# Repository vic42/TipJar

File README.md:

# TipJar
Vienna Repair Cafe talking tip jar

DESCRIPTION
===========

This is a *talking* tip jar design that is able to differentiate between coins and banknotes to utter two different spoken, sung or screamed messages accordingly.
It is a Lo-Fi approach meant to reduce cost as well as programming effort in order to get it done and ultimately keep it easily reproducible.
Feel free to use and/or comment.

# HOW IT WORKS

The board detects objects in the gap of two photointerrupters and measures the time than an object spends to pass the photointerrupters. If the time is below a certain threshold a coin is detected and one of the sound modules gets activated. if the time is above that threshold a banknote is detected and the other sound module is activated.
This way two different sound messages are played depending on the type of cash thrown into the tip jar.

# HARDWARE

The hardware is prepared for two modes of sound generation:

* sound recorded on one or two Chinese sound modules (e.g. 2 x ISD1820)
* sound generation by the microcontroller itself

Depending on which mode you prefer you can omit some of the components on the PCB

* first option: R7, D2, L2, C5, L1, C3, P2
* second option: BT1, D3, D4, R8, R10, Q3, Q6, P4, P5

There are various options powering the circuit:

* LiPo battery with micro USB power supply as charger
* 5V micro USB power supply only

Depending on if you need battery supply you can leave out some components

* with battery: U2
* without battery: U1, R1, R2, R3, JP1, P3

Warning: the PN2222A SOT23 footprint of the current PCB has base and emitter swapped.

# SOFTWARE

Currently there is a simplistic C program in the repository that switches on the optointerrupters for 1 ms every 10 ms (10% duty cycle saves power) to see if one of them is interrupted by an object. if so, it counts the cycles while the object occludes the detector. If 8 cycles have passed before the detector sees light again a banknote is assumed to have passed the detector. Oterwise the object detected is assumed to have been a coin.

# BUILD

There is a Makefile included with the code. It needs to be adjusted to your AVR-ISP interface in order to upload the code to the microcontroller directly.

# SEE ALSO

* https://repaircafe.wien/

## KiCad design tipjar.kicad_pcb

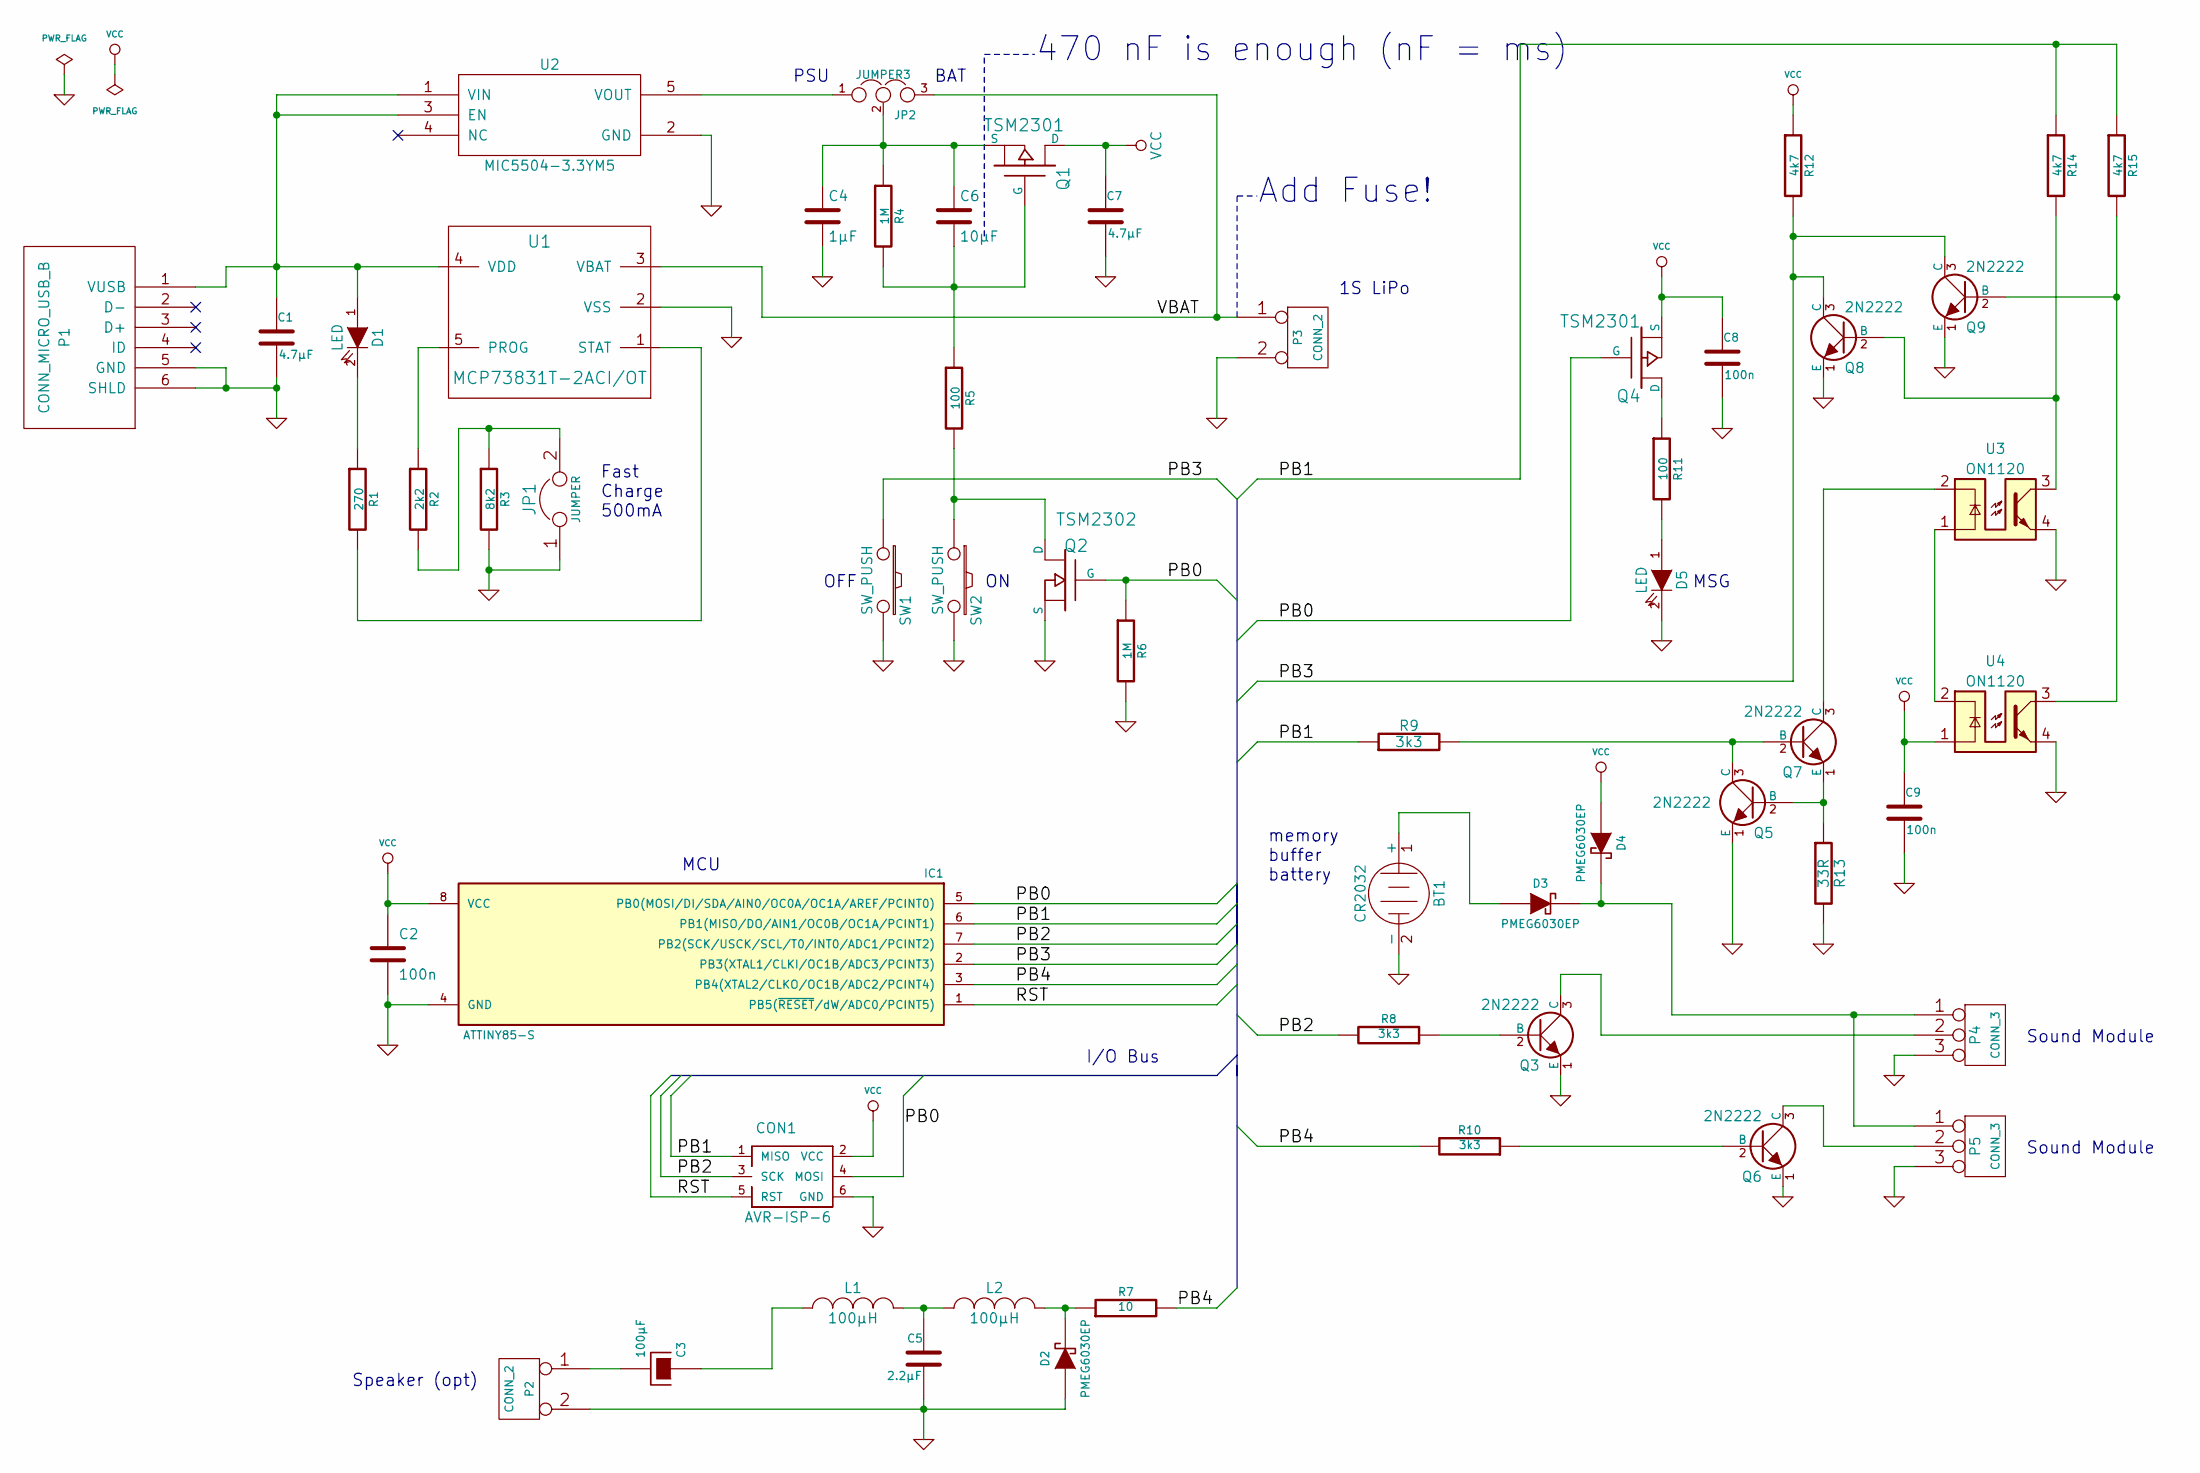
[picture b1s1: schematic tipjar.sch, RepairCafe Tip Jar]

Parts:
BT1: CR2032; Keystone_3034_1x20mm-CoinCell
C1, C7: 4.7µF; C_0805
C2, C8, C9: 100n; C_0603
C3: 100µF; CP_Elec_6.3x7.7
C4: 1µF; C_0805
C5: 2.2µF; C_0805
C6: 10µF; C_0805
CON1: AVR-ISP-6; Pin_Header_Straight_2x03_Pitch2.54mm
D1, D5: LED; LED_0603
D2, D3, D4: PMEG6030EP; SOD-128
IC1: ATTINY85-S; SOIC127P798X216-8N
JP1: JUMPER; Pin_Header_Straight_1x02_Pitch2.54mm
JP2: JUMPER3; Pin_Header_Straight_1x03_Pitch2.54mm
L1, L2: 100µH; L_12x12mm_h8mm
P1: CONN_MICRO_USB_B; MICRO-B_USB
P2: CONN_2; Pin_Header_Straight_1x02_Pitch2.54mm
P3: CONN_2; JST_XH_B02B-XH-A_02x2.50mm_Straight
P4, P5: CONN_3; Pin_Header_Straight_1x03_Pitch2.54mm
Q1, Q4: TSM2301; SOT-23
Q2: TSM2302; SOT-23
Q3, Q5, Q6, Q7, Q8, Q9: 2N2222; SOT-23
R1: 270; R_0603
R2: 2k2; R_0603
R3: 8k2; R_0603
R4, R6: 1M; R_0603
R5, R11: 100; R_0603
R7: 10; R_0805_HandSoldering
R8, R9, R10: 3k3; R_0603
R12, R14, R15: 4k7; R_0603
R13: 33R; R_0603
SW1, SW2: SW_PUSH; SW_SPST_EVQPE1
U1: MCP73831T-2ACI/OT; SOT-23-5
U2: MIC5504-3.3YM5; SOT-23-5
U3, U4: ON1120

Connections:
/PB0: CON1.4 (MOSI), IC1.5 (PB0(MOSI/DI/SDA/AIN0/OC0A/OC1A/AREF/PCI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), Q2.1 (G), Q4.1 (G), R6.1
/PB1: CON1.1 (MISO), IC1.6 (PB1(MISO/DO/AIN1/OC0B/OC1A/PCINT1)), R9.1, R14.1, R15.1
/PB2: CON1.3 (SCK), IC1.7 (PB2(SCK/USCK/SCL/T0/INT0/ADC1/PCINT2)), R8.2
/PB3: IC1.2 (PB3(XTAL1/CLKI/OC1B/ADC3/PCINT3)), Q8.3 (C), Q9.3 (C), R12.2, SW1.1
/PB4: IC1.3 (PB4(XTAL2/CLKO/OC1B/ADC2/PCINT4)), R7.2, R10.2
/RST: CON1.5 (RST), IC1.1 (PB5(~RESET~/dW/ADC0/PCINT5))
/VBAT: JP2.3, P3.1, U1.3 (VBAT)
GND: BT1.2 (-), C1.2, C2.2, C4.2, C5.2, C7.2, C8.2, C9.2, CON1.6 (GND), D2.1 (A), D5.2 (K), IC1.4 (GND), JP1.1, P1.5 (GND), P1.6 (SHLD), P2.2 (PM), P3.2 (PM), P4.3, P5.3, Q2.2 (S), Q3.1 (E), Q5.1 (E), Q6.1 (E), Q8.1 (E), Q9.1 (E), R3.2, R6.2, R13.2, SW1.2, SW2.2, U1.2 (VSS), U2.2 (GND), U3.4, U4.4
unnamed: BT1.1 (+), D3.1 (A)
unnamed: C1.1, D1.1 (A), P1.1 (VUSB), U1.4 (VDD), U2.1 (VIN), U2.3 (EN)
unnamed: C3.1, L1.2
unnamed: C3.2, P2.1
unnamed: C4.1, C6.1, JP2.2, Q1.2 (S), R4.1
unnamed: C5.1, L1.1, L2.2
unnamed: C6.2, Q1.1 (G), R4.2, R5.1
unnamed: D1.2 (K), R1.1
unnamed: D2.2 (K), L2.1, R7.1
unnamed: D3.2 (K), D4.2 (K), P4.1, P5.1
unnamed: D5.1 (A), R11.2
unnamed: JP1.2, R2.2, R3.1
unnamed: JP2.1, U2.5 (VOUT)
unnamed: P4.2 (PM), Q3.3 (C)
unnamed: P5.2 (PM), Q6.3 (C)
unnamed: Q2.3 (D), R5.2, SW2.1
unnamed: Q3.2 (B), R8.1
unnamed: Q4.3 (D), R11.1
unnamed: Q5.2 (B), Q7.1 (E), R13.1
unnamed: Q5.3 (C), Q7.2 (B), R9.2
unnamed: Q6.2 (B), R10.1
unnamed: Q7.3 (C), U3.2
unnamed: Q8.2 (B), R14.2, U3.3
unnamed: Q9.2 (B), R15.2, U4.3
unnamed: R1.2, U1.1 (STAT)
unnamed: R2.1, U1.5 (PROG)
unnamed: U3.1, U4.2
VCC: C2.1, C7.1, C8.1, C9.1, CON1.2 (VCC), D4.1 (A), IC1.8 (VCC), Q1.3 (D), Q4.2 (S), R12.1, U4.1

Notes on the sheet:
1S LiPo
Sound Module
BAT
PSU
MCU
OFF
MSG
Fast Charge 500mA
I/O Bus
Speaker (opt)
memory buffer battery
470 nF is enough (nF = ms)
Add Fuse!

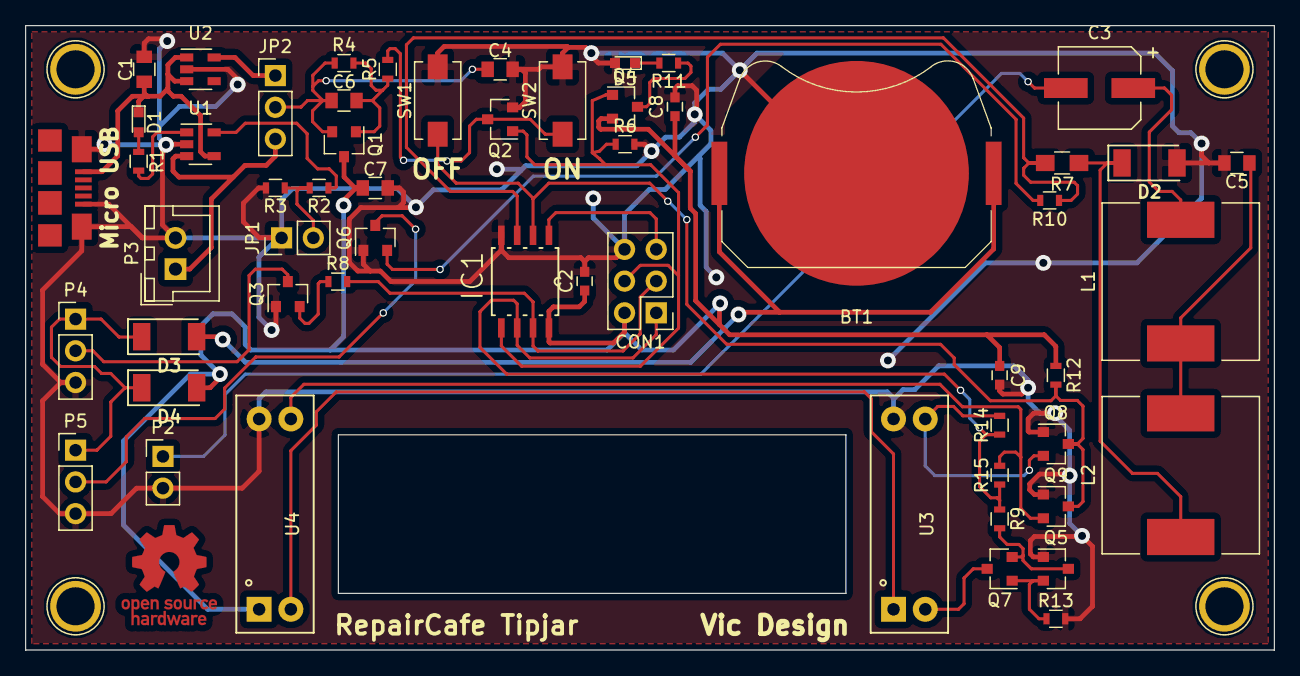
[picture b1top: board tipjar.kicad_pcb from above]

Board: 2 copper layers, 100.0 x 50.0 mm, 56 parts (0 on the bottom side), 36 nets.

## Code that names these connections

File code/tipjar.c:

/* The RepairCafe TipJar, Copyright (c)2017-2019 Peter Franck
 * 
 * This program is free software: you can redistribute it and/or modify
 * it under the terms of the GNU General Public License as published by
 * the Free Software Foundation, either version 3 of the License, or
 * (at your option) any later version.
 * 
 * This program is distributed in the hope that it will be useful,
 * but WITHOUT ANY WARRANTY; without even the implied warranty of
 * MERCHANTABILITY or FITNESS FOR A PARTICULAR PURPOSE.  See the
 * GNU General Public License for more details.
 * You should have received a copy of the GNU General Public License
 * along with this program.  If not, see <http://www.gnu.org/licenses/>.
 */

#define F_CPU	8000000UL
#include <avr/io.h>
#include <util/delay.h>
#include <avr/interrupt.h>

#define set(x) |= (1<<x)
#define clr(x) &=~(1<<x)
#define inv(x) ^=(1<<x)

/* port B pin definitions */
#define SND1	PB2		// sound module 1 trigger pin
#define SND2	PB4		// sound module 2 trigger pin
#define SNDOUT	PB4		// sound waveform output pin
#define PWRLED	PB0		// HIGH=hold power, LOW=light message LED
#define PHOTR	PB3		// photo transistor input
#define PWROFF	PB3		// power off switch input (muxed)
#define IRLED	PB1		// HIGH=IR LEDs on

void init(void);

int is_interrupted(void)	// return 1 if photointerrupter dark
{
	int pintr;
	
	PORTB set(IRLED);		// switch on IR LEDs
	_delay_ms(1);			// wait for IR to settle
	pintr = !(PINB & (1<<PHOTR));	// read the photo interrupter
	PORTB clr(IRLED);		// switch off IR LEDs (save power)
	return pintr;
}

int vcc_low(void)			// return 0 if VCC OK, != 0 if VCC low
{
	volatile long result;
	
	ADCSRA |= _BV(ADSC);			// Start conversion
	loop_until_bit_is_set(ADCSRA,ADSC);	// measuring
	result = ADC;
	result = 1126400L / result;		// Calculate Vcc (in mV); 1126400 = 1.1*1024*1000
	return (result < 3100L);		// Vcc < 3.1V
}

void main(void) {
	int sound=0;
	
	init();

	for(;;) {				// endless loop
		PORTB set(PWRLED);		// hold power, LED off
		_delay_ms(8);			// defines the PWM off-time for the power LED
		PORTB clr(PWRLED);
		_delay_ms(1);			// defines the PWM on-time for the power LED

		/* power off if switch pressed or low voltage */
		if ( !(PINB & (1<<PWROFF)) || vcc_low() ) {	// read the off switch and VCC
			PORTB set(IRLED);
			PORTB clr(PWRLED);	// switch power hold off (LED on)
			for(;;);		// halt
		}

		/* read photo interrupters */
		if (is_interrupted()) {
			++sound;
			if ( sound >= 8 ) 	{	// long sample
				sound=0;
				PORTB set(PWRLED);	// hold power, LED off
				PORTB set(SND1);
				_delay_ms(1);
				PORTB clr(SND1);
				_delay_ms(1000);
			}
		}
		else if (sound) {		// short sample
			sound=0;
			PORTB set(PWRLED);	// hold power, LED off
			PORTB set(SND2);
			_delay_ms(1);
			PORTB clr(SND2);
			_delay_ms(1000);
		}
	}
}

void init(void) {
	// set the direction of the ports
	DDRB set(PWRLED);	// PWR/LED OUTPUT
	DDRB set(SND1);		// sound module 1 OUTPUT
	DDRB set(SND2);		// sound module 2 OUTPUT
	DDRB set(IRLED);	// infrared sensor LEDs OUTPUT
	DDRB clr(PHOTR);	// phototransistor INPUT
	PORTB set(PHOTR);	// enable pullup resistor

	CLKPR = (1 << CLKPCE);	// enable clock prescaler update
	CLKPR = 0;		// set clock to maximum (= crystal/RC oscillator)
	
	PORTB clr(PWRLED);	// LED=on
	_delay_ms(700);		// avoid self-switch-on
	PORTB set(PWRLED);	// self-hold power switch (LED=off)
	PORTB set(SND1);	// set sound module inputs to LOW
	PORTB set(SND2);
	
	ADCSRA = _BV(ADEN);			// enable ADC
	ADMUX = _BV(MUX3) | _BV(MUX2);		// set ADC reference to Vcc and input internal 1.1V reference
	_delay_ms(1);				// wait for reference to settle
	ADCSRA |= _BV(ADSC);			// Start dummy ADC conversion
	loop_until_bit_is_set(ADCSRA,ADSC);	// measuring
}

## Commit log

2017-11-01 initial upload of very first attempt
2017-11-01 Add lithium battery for data retention
2019-11-25 First remote commit
2019-11-26 tested software
2019-11-26 description improved
2019-11-27 minor software changes
2019-11-27 update gitignore
2019-12-03 timing stuff
2019-12-03 more timing stuff
2019-12-06 minor updates
